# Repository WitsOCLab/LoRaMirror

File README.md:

# LoRaMirror

A lovely LoRa powered remote controlled mirror

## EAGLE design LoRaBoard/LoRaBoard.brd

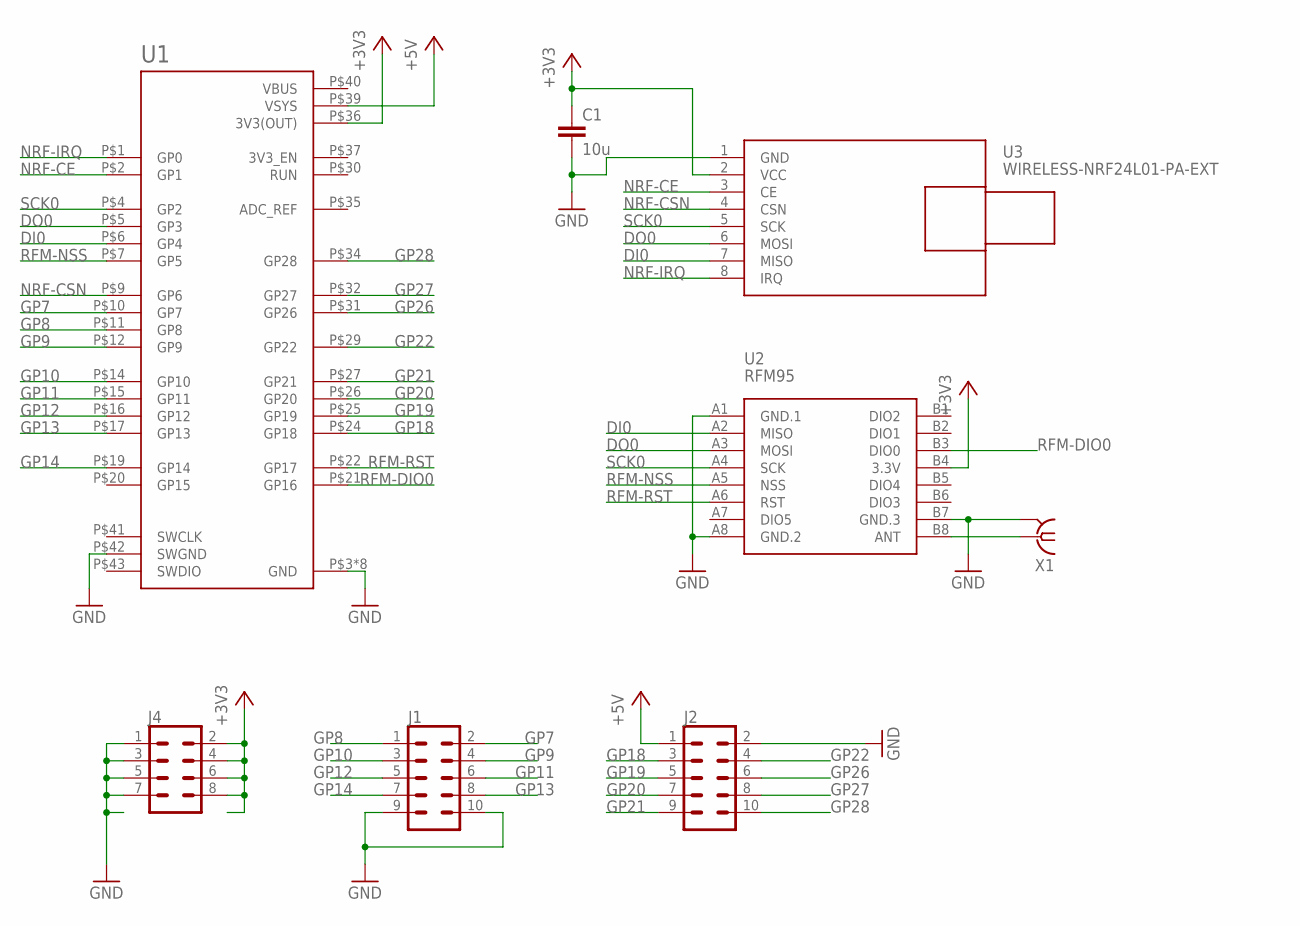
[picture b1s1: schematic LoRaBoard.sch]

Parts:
C1: 10u; C0805
J1, J2: CONN_05X2PTH; 2X5
J4: CONN_04X2; 2X4
U1: RASPBERRY_PICOSMD; PICO-PKG-SMD
U2: RFM95; WIRELESS-LORA-RFM95W#SMD
U3: WIRELESS-NRF24L01-PA-EXT
X1: SMA-142-0701-801/806; J502-ND-142-0701-801/806

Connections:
+3V3: C1.1, J4.2, J4.4, J4.6, J4.8, U1.P$36 (3V3(OUT)), U2.B4 (3.3V), U3.2 (VCC)
+5V: J2.1, U1.P$39 (VSYS)
DI0: U1.P$6 (GP4), U2.A2 (MISO), U3.7 (MISO)
DO0: U1.P$5 (GP3), U2.A3 (MOSI), U3.6 (MOSI)
GND: C1.2, J1.9, J1.10, J2.2, J4.1, J4.3, J4.5, J4.7, U1.P$3 (GND), U1.P$8 (GND), U1.P$13 (GND), U1.P$18 (GND), U1.P$23 (GND), U1.P$28 (GND), U1.P$33 (GND), U1.P$38 (GND), U1.P$42 (SWGND), U2.A1 (GND.1), U2.A8 (GND.2), U2.B7 (GND.3), U3.1 (GND), X1.G@1 (2), X1.G@2 (2), X1.G@3 (2), X1.G@4 (2)
GP7: J1.2, U1.P$10 (GP7)
GP8: J1.1, U1.P$11 (GP8)
GP9: J1.4, U1.P$12 (GP9)
GP10: J1.3, U1.P$14 (GP10)
GP11: J1.6, U1.P$15 (GP11)
GP12: J1.5, U1.P$16 (GP12)
GP13: J1.8, U1.P$17 (GP13)
GP14: J1.7, U1.P$19 (GP14)
GP18: J2.3, U1.P$24 (GP18)
GP19: J2.5, U1.P$25 (GP19)
GP20: J2.7, U1.P$26 (GP20)
GP21: J2.9, U1.P$27 (GP21)
GP22: J2.4, U1.P$29 (GP22)
GP26: J2.6, U1.P$31 (GP26)
GP27: J2.8, U1.P$32 (GP27)
GP28: J2.10, U1.P$34 (GP28)
unnamed: U2.B8 (ANT), X1.1
NRF-CE: U1.P$2 (GP1), U3.3 (CE)
NRF-CSN: U1.P$9 (GP6), U3.4 (CSN)
NRF-IRQ: U1.P$1 (GP0), U3.8 (IRQ)
RFM-DIO0: U1.P$21 (GP16), U2.B3 (DIO0)
RFM-NSS: U1.P$7 (GP5), U2.A5 (NSS)
RFM-RST: U1.P$22 (GP17), U2.A6 (RST)
SCK0: U1.P$4 (GP2), U2.A4 (SCK), U3.5 (SCK)
VBUS: U1.P$40 (VBUS)

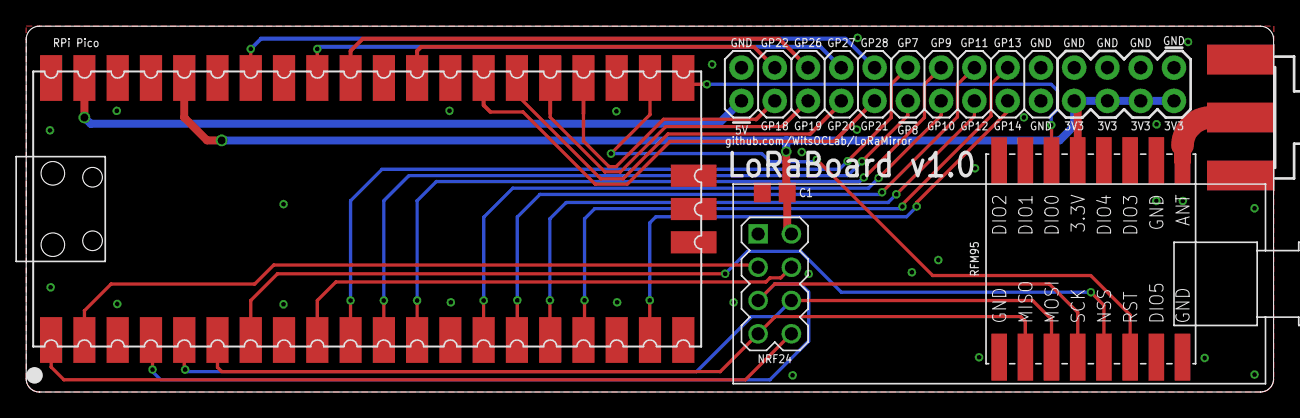
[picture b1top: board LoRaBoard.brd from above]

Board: 2 copper layers, 95.2 x 27.9 mm, 8 parts (0 on the bottom side), 29 nets.

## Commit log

2021-02-09 intiial
2021-02-09 original
2021-02-11 working
2021-02-15 working quite well
2021-05-07 added hardware with nrf and rfm
2021-06-01 pi pico started
2021-11-30 Create LICENSE
2022-02-05 Transition to PIO
2022-02-06 Add CommunicationProtocol Class
2022-02-06 Implemented new comms protocol
2022-02-09 Continued bringup
2022-02-09 Added classes to remote
2022-02-09 Add remote models
2022-02-10 Add heartbeat index checks
2022-02-10 Mirror stable
2022-02-14 Revamped joystick API and Remote always follows mirror state
2022-02-16 Improved Interface
2022-02-16 Can now enter settings from idle
2022-02-21 Adjust remote battery voltage calculation

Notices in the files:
parts and their libraries:
diy-modules: Released under the Creative Commons Attribution 4.0 International License: http://creativecommons.org/licenses/by/4.0
SparkFun-Connectors: Licensing: Creative Commons ShareAlike 4.0 International - https://creativecommons.org/licenses/by-sa/4.0
